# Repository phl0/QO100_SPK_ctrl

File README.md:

# QO100_SPK_ctrl
Speaker control unit for full-duplex satellite operations for the sake of demonstration

This circuit is designed to control the speaker level of a full-duplex satellite station during transmissions. It was originally designed to be used for a club station in order to demonstrate full-duplex satellite operations with audio output via speaker. In order to attenuate the audio level during transmissions to avoid feedback the audio line is attenuated with a 49-ohm potentiometer. The switching between RX and TX is done via PTT output of the TRX.

## Schematics

The [circuit schematics](QO100_SPK_ctrl.svg) is a simple relay switch using two PNP transistors. For manual control two switches are added so that the speaker attenuation as well as the PTT line of the UpConverter can be switched manually.

## Bill of Materials

The [few parts](QO100_SPK_ctrl.xlsx) can be grabbed from the spare parts box. For other purposes there is a shopping cart at German distributor Reichelt Eletronik. See [here](https://www.reichelt.de/my/1923061). This does not include the relay. Few of those can be obtained from the author. Same goes for the PCB itself. The LEDs as well as the trimmer are layouted as 2.54mm connectors so that the parts itself can be mounted in a case.

The [interactive BOM](https://www.df2et.de/QO100_SPK_ctrl/ibom.html) for sourcing and placing the parts can be found in the bom folder of this project.

## Known Issues

### v0.5
The v0.5 PCB and circuit were missing diode D4. Due to this the PTT transistor was pulled low by the UpConverter. This error has been corrected in v0.6.

### v0.6
The diode D4 has been added. This PCB rev is missing the 4 drill holes on the PCB edges.

### v0.7
The missing drill hole for mounting have been re-added.

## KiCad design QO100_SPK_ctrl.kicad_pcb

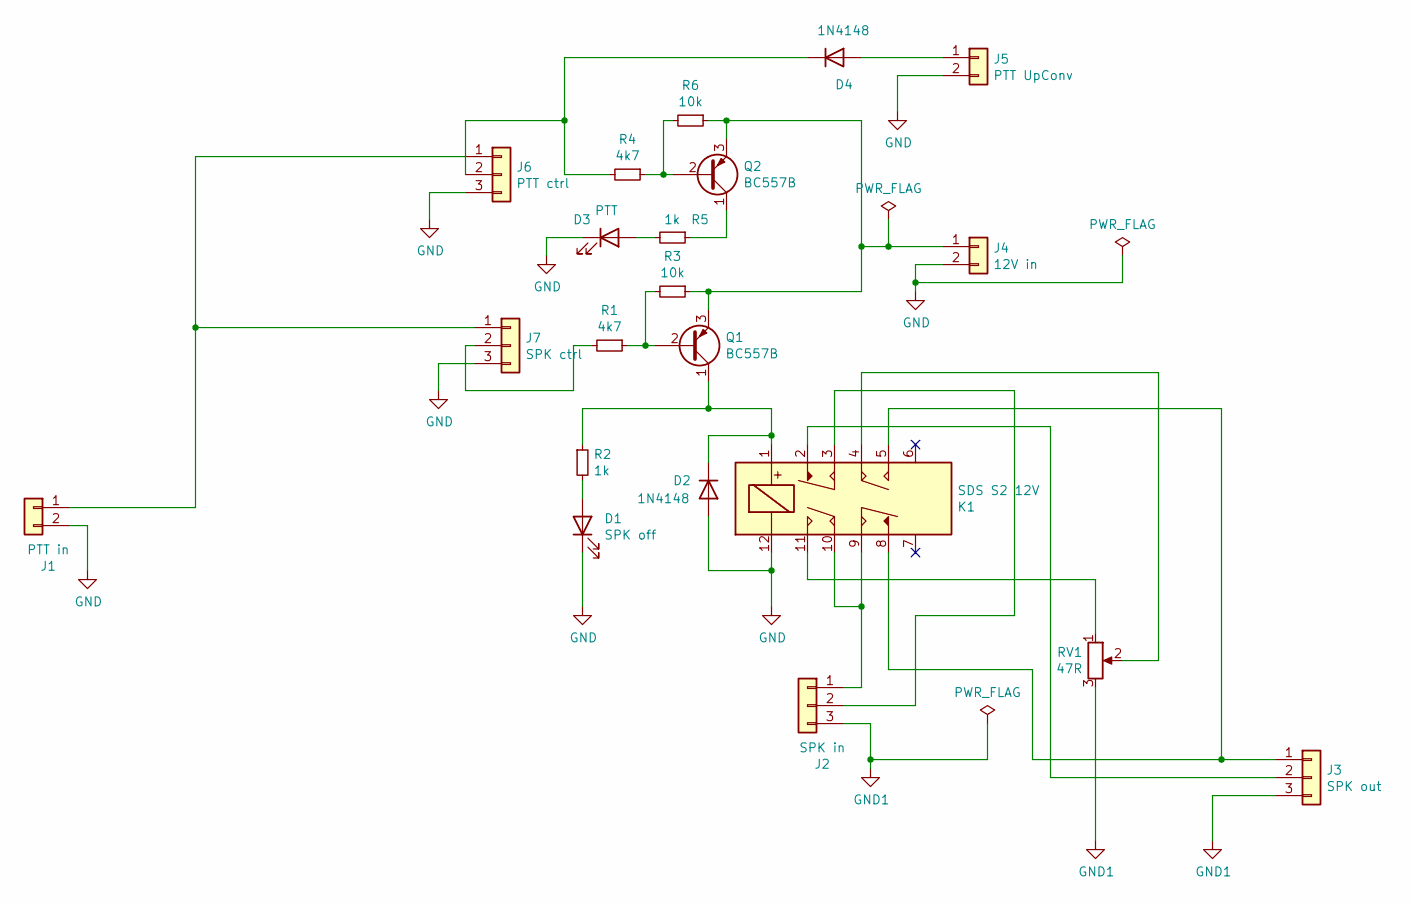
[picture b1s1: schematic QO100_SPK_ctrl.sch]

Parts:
D1: SPK off; PinHeader_1x02_P2.54mm_Vertical; MPN 10120919
D2, D4: 1N4148; D_DO-35_SOD27_P7.62mm_Horizontal; MPN RND 1N4148
D3: PTT; PinHeader_1x02_P2.54mm_Vertical; MPN 10120919
J1: PTT in; PinHeader_1x02_P2.54mm_Vertical; MPN 10120919
J2: SPK in; PinHeader_1x03_P2.54mm_Vertical; MPN 10120200
J3: SPK out; PinHeader_1x03_P2.54mm_Vertical; MPN 10120200
J4: 12V in; PinHeader_1x02_P2.54mm_Vertical; MPN 10120919
J5: PTT UpConv; PinHeader_1x02_P2.54mm_Vertical; MPN 10120919
J6: PTT ctrl; PinHeader_1x03_P2.54mm_Vertical; MPN 10120200
J7: SPK ctrl; PinHeader_1x03_P2.54mm_Vertical; MPN 10120200
K1: SDS S2 12V; Relay_SDS_S2; MPN S2-DC12V
Q1, Q2: BC557B; TO-92; MPN BC 557B
R1, R4: 4k7; R_Axial_DIN0204_L3.6mm_D1.6mm_P5.08mm_Horizontal; MPN 1/4W 4,7K
R2, R5: 1k; R_Axial_DIN0204_L3.6mm_D1.6mm_P5.08mm_Horizontal; MPN 1/4W 1,0K
R3, R6: 10k; R_Axial_DIN0204_L3.6mm_D1.6mm_P5.08mm_Horizontal; MPN 1/4W 10K
RV1: 47R; PinHeader_1x03_P2.54mm_Vertical; MPN P4W-LIN 47

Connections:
GND: D1.1 (K), D2.2 (A), D3.1 (K), J1.2, J4.2, J5.2, J6.3, J7.3, K1.12
GND1: J2.3, J3.3, RV1.3
unnamed: D1.2 (A), R2.2
unnamed: D2.1 (K), K1.1, Q1.1 (C), R2.1
unnamed: D3.2 (A), R5.2
unnamed: D4.1 (K), J6.2, R4.2
unnamed: D4.2 (A), J5.1
unnamed: J1.1, J6.1, J7.1
unnamed: J2.1, K1.9, K1.10
unnamed: J2.2, K1.3
unnamed: J3.1, K1.5, K1.8
unnamed: J3.2, K1.2
unnamed: J4.1, Q1.3 (E), Q2.3 (E), R3.1, R6.1
unnamed: J7.2, R1.2
unnamed: K1.4, RV1.2
unnamed: K1.11, RV1.1
unnamed: Q1.2 (B), R1.1, R3.2
unnamed: Q2.1 (C), R5.1
unnamed: Q2.2 (B), R4.1, R6.2

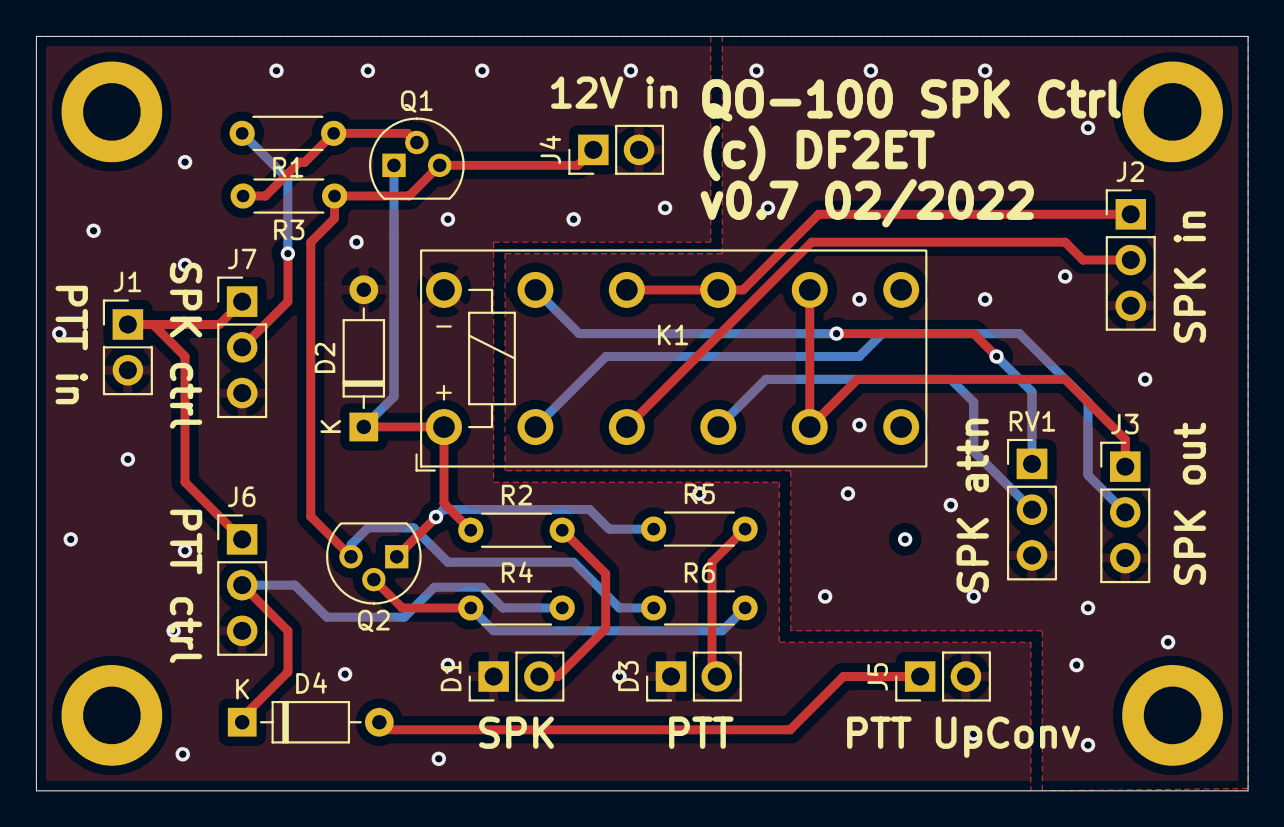
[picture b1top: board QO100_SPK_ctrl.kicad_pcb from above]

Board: 2 copper layers, 67.3 x 41.9 mm, 21 parts (0 on the bottom side), 19 nets.

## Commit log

2022-02-07 Update link to ibom
2022-02-07 Re-add drill holes for mounting
2022-02-07 Update ibom
2022-07-10 Add panel designs
